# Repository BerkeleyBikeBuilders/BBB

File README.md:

# Telemetry Computer

## Description
This repository contains the HW and FW related to the ESP32 telemetry computer V1 (Fall 2023 - Fall 2024)

## Installation
1. Clone the repository:
   
    Go to the folder you want to clone to, and:
    ```bash
    git clone https://github.com/BerkeleyBikeBuilders/TelemetryComputer.git

3. Install IDE:
   
    **Platform IO on VS Code**
   
    Install Platform IO extension on VSCode, or the Arduino IDE online.

    **Arduino IDE**
   
    Install IDE from here: https://www.arduino.cc/en/software
   
    Add ESP32 boards this way: https://randomnerdtutorials.com/vs-code-platformio-ide-esp32-esp8266-arduino/
   
    If you prefer to use the Arduino IDE, to access the project, edit the 'telemetryINO' project, **and remember to first update the code from src/main.cpp**

4. install Libraries:
    I think it's only nessesary for the Arduino IDE.
    - Adafruit BusIO

6. select boards:
    Select either "Adafruit ESP32 Feather" or "WEMOS LOLIN32 Lite"

## Debugging
1. .............A fatal error occurred: No serial data received
   
   Try Changing to upload speed to 115200
   
   Try pressing the reset button, can also help clear processes that's preventing the upload (check your code).

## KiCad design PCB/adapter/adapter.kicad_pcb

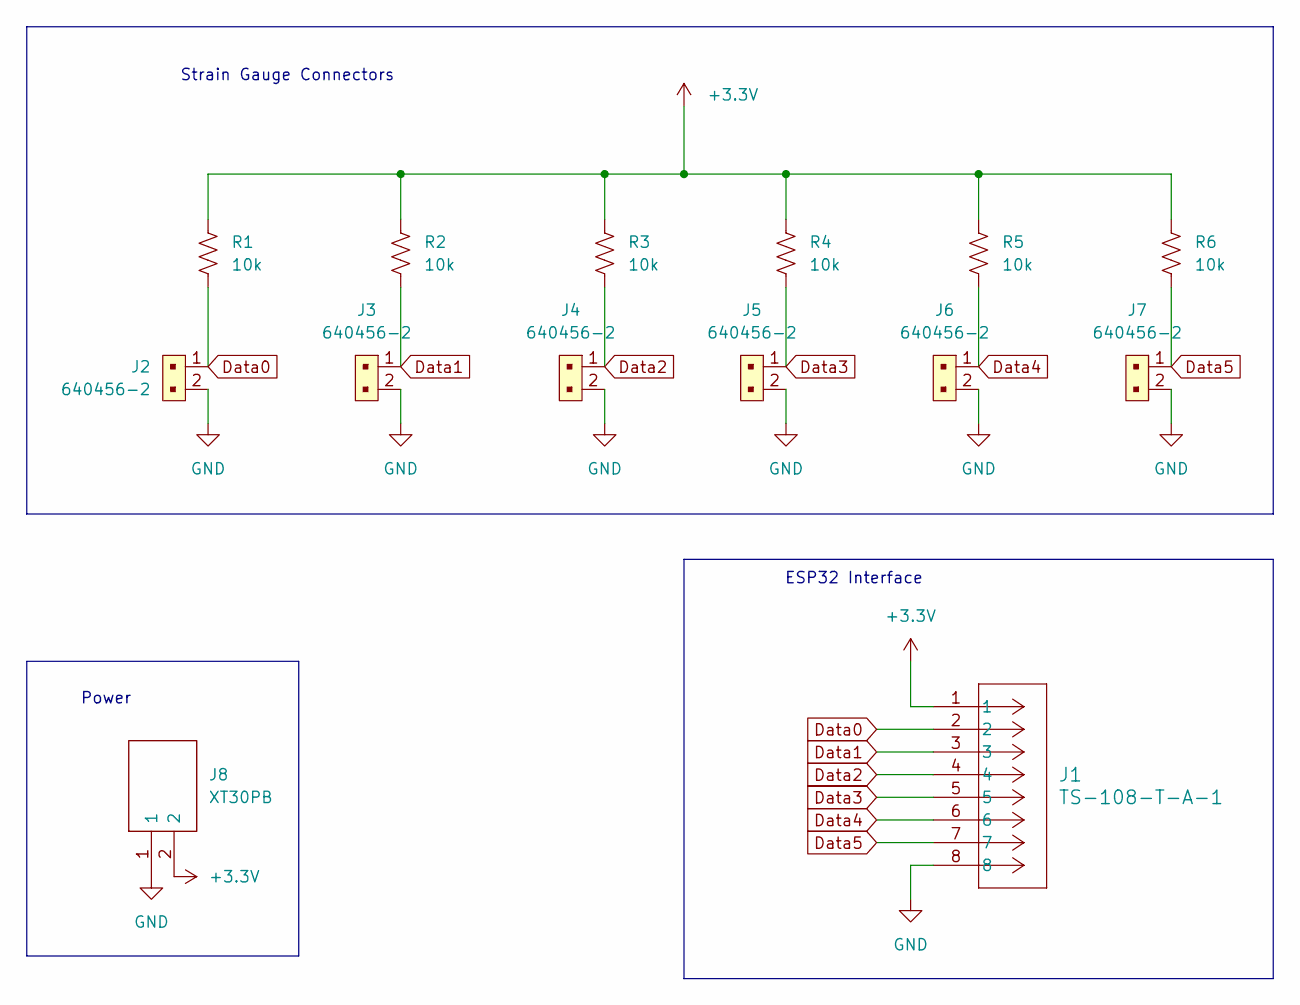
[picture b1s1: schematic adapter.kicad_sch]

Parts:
J1: TS-108-T-A-1; CON8_1X8_TUC_HTS_SAI
J2, J3, J4, J5, J6, J7: 640456-2; PinHeader_1x2_P2.54mm_Drill1.02mm; MPN 640456-2; Digi-Key_PN A1921-ND
J8: XT30PB; AMASS_XT30U-F_1x02_P5.0mm_Vertical; Manufacturer_Part_Number XT30PB
R1, R2, R3, R4, R5, R6: 10k; R_0603_1608Metric

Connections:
+3.3V: J1.1, J8.2, R1.1, R2.1, R3.1, R4.1, R5.1, R6.1
Data0: J1.2, J2.1, R1.2
Data1: J1.3, J3.1, R2.2
Data2: J1.4, J4.1, R3.2
Data3: J1.5, J5.1, R4.2
Data4: J1.6, J6.1, R5.2
Data5: J1.7, J7.1, R6.2
GND: J1.8, J2.2, J3.2, J4.2, J5.2, J6.2, J7.2, J8.1

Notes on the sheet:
Power
ESP32 Interface
Strain Gauge Connectors

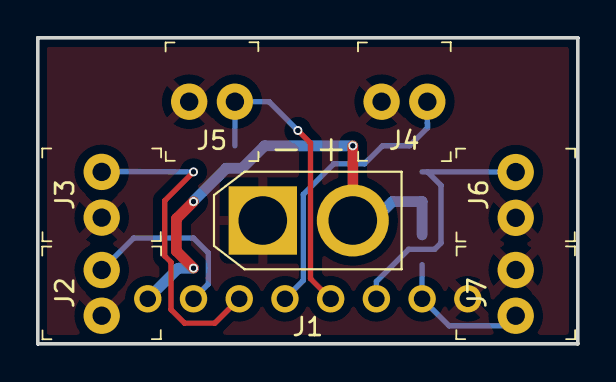
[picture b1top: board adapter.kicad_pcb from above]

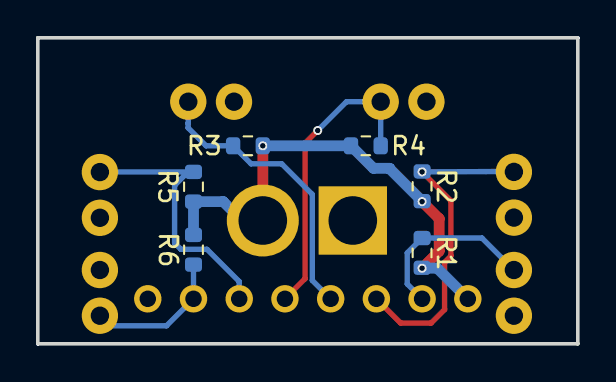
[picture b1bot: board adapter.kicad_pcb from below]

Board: 2 copper layers, 30.0 x 17.0 mm, 14 parts (6 on the bottom side), 8 nets.

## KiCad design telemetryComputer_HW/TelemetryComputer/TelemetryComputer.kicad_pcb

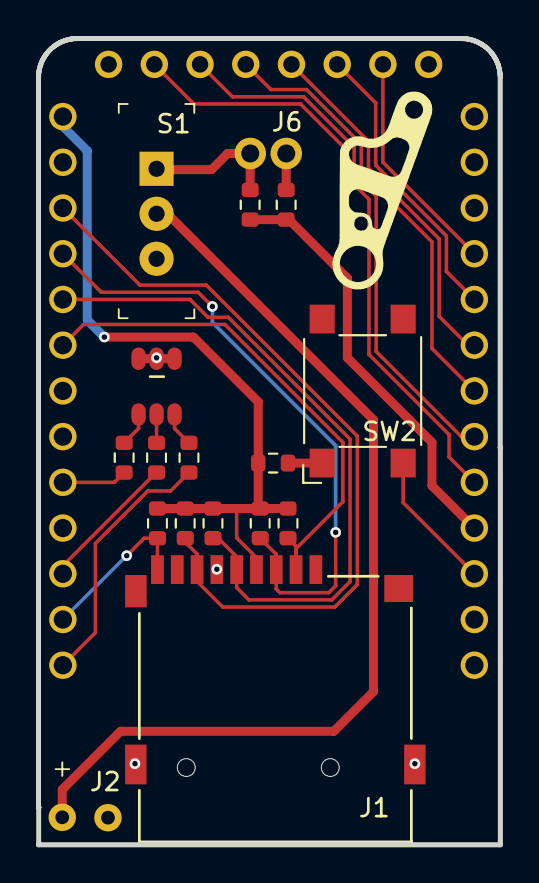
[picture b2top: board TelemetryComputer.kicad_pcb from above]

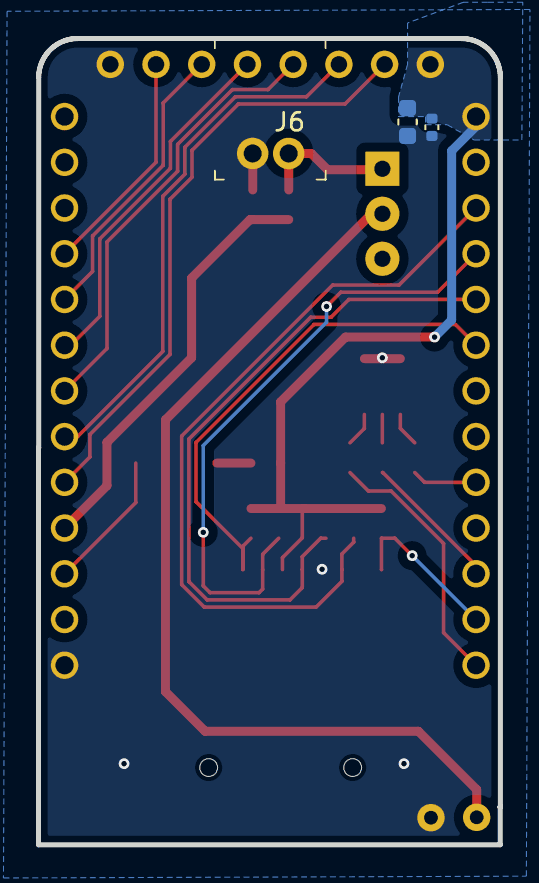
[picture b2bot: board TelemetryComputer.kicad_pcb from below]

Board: 2 copper layers, 25.7 x 44.8 mm, 22 parts (3 on the bottom side), 24 nets.

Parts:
C2: 10uF; C_0603_1608Metric
C3: 0.1uF; C_0402_1005Metric
D1: CLX6F-FKC-CKNNQDGBB7A363; SOJ100P350X290-6N
J1: MSD-1-A; CONN9_MSD-1_CUD
J2: M20-9990246; PinHeader_1x2_P2.54mm
J3, J4: SSW-113-01-T-S-LL; CON13_1X13_TU_SSQ
J5: TS-108-T-A-1; CON8_1X8_TUC_HTS_SAI
J6: S2B-PH-K-S_LF__SN_; PinHeader_1x2_P2mm_Drill1mm_RA
R1, R2, R3, R4, R5, R12: 10k; R_0603_1608Metric
R6, R7: 47k; R_0603_1608Metric
R8, R9, R10: 470; R_0603_1608Metric
S1: EG1218; Switch_Slide_11.6x4mm_EG1218
SW2: SW_Omron_B3FS; SW_SPST_Omron_B3FS-100xP

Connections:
+3.3V: C2.1, C3.1, J1.4 (VDD), J3.1, J5.1, R1.1, R2.1, R3.1, R4.1, R5.1, R12.1
BAT+: J2.2, S1.2
BAT-: C2.2, C3.2, D1.1, D1.2, D1.3, J1.6 (VSS), J1.10 (Shield), J1.11 (Shield), J2.1, J4.13, J5.8, J6.2, R7.2
BAT_ADC: J4.10, R6.2, R7.1
BLUE: J3.13, R8.1
BUTTON: J4.11, SW2.2
CD: J1.CD, J3.12, R5.2
CLK: J1.5 (CLK), J3.5, R3.2
CS: J1.2 (CD/DAT3), J3.6, R1.2
GPIO_25: J4.8, J5.3
GPIO_26: J4.9, J5.2
GPIO_32: J4.6, J5.5
GPIO_33: J4.7, J5.4
GPIO_34: J4.4, J5.7
GPIO_35: J4.5, J5.6
GREEN: J3.11, R9.1
MISO: J1.7 (DAT0), J3.3, R4.2
MOSI: J1.3 (CMD), J3.4, R2.2
unnamed: D1.4, R10.2
unnamed: D1.5, R9.2
unnamed: D1.6, R8.2
unnamed: J6.1, R6.1, S1.1
unnamed: R12.2, SW2.1
RED: J3.9, R10.1

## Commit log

2023-12-15 Create LICENSE
2023-12-15 Create info
2023-12-15 Added code so far for ESP32
2023-12-15 Update info
2023-12-15 Create Full Sus Telemetry
2023-12-15 Create about
2023-12-15 Arduino files so far
2024-01-27 Updated file
2024-01-27 Bru if this doesn't work...
2024-03-02 Code worked for Kevin
2024-03-02 Code that worked for Kevin
2024-03-02 variables fixed?
2024-03-03 added ID# and compareTo method
2024-04-11 updated code
2024-05-15 stuff updated
2024-05-15 format updated
2024-07-06 SD card corrected to VSPI pins
    MOSI: Pin 23
    MISO: Pin 19
    CLK: Pin 18
    CS: Pin 5
2024-07-10 added languages
2024-07-14 minor tweaks
2024-07-17 added Platform IO project
2024-07-17 added PIO
2024-07-17 its done
2024-07-17 Create BBB-Software-Things.code-workspace
2024-07-30 changed indicator lights
2024-07-31 added custom RGB colours
2024-07-31 formatting
2024-08-22 updated documentation & changed macros to enum
2024-08-23 big changes
2024-08-23 fixed brightness controls
2024-08-28 Ready for Fall 2024!
2024-08-28 Revert "Ready for Fall 2024!"
    This reverts commit a9809f8729a649ef2c50adf7f5f72ee82b5d9a48.
2024-08-28 Reapply "Ready for Fall 2024!"
    This reverts commit e58cfe65e1959bf659cb108c39cd2d223e135f0e.
2024-08-28 moved to new folder
2024-08-28 Work in progress
2024-08-28 still work in progress
2024-08-28 still working progree
2024-08-28 fixed link
2024-10-24 updated INO file
2024-10-25 added PCB schematic
2024-10-25 added more KiCAD stuff
2024-10-30 pushed!
2024-11-07 added mock data
2024-11-11 made calibration its own thing
2024-11-11 semicolon :)
2024-11-14 CSV for one strain gauge
2024-11-15 3 Strain Gauges
2024-11-27 cleaned up some code
2024-11-27 Lib gone
2024-12-03 Experimental reformat/organization
    Mostly w/ GPT
2024-12-04 modifications to LED Behaviors sleep func and main.cpp for new func names
2025-07-22 reorganised files
2025-07-22 more reorgnaising
2025-07-23 moved things
2025-07-23 reverted changes
